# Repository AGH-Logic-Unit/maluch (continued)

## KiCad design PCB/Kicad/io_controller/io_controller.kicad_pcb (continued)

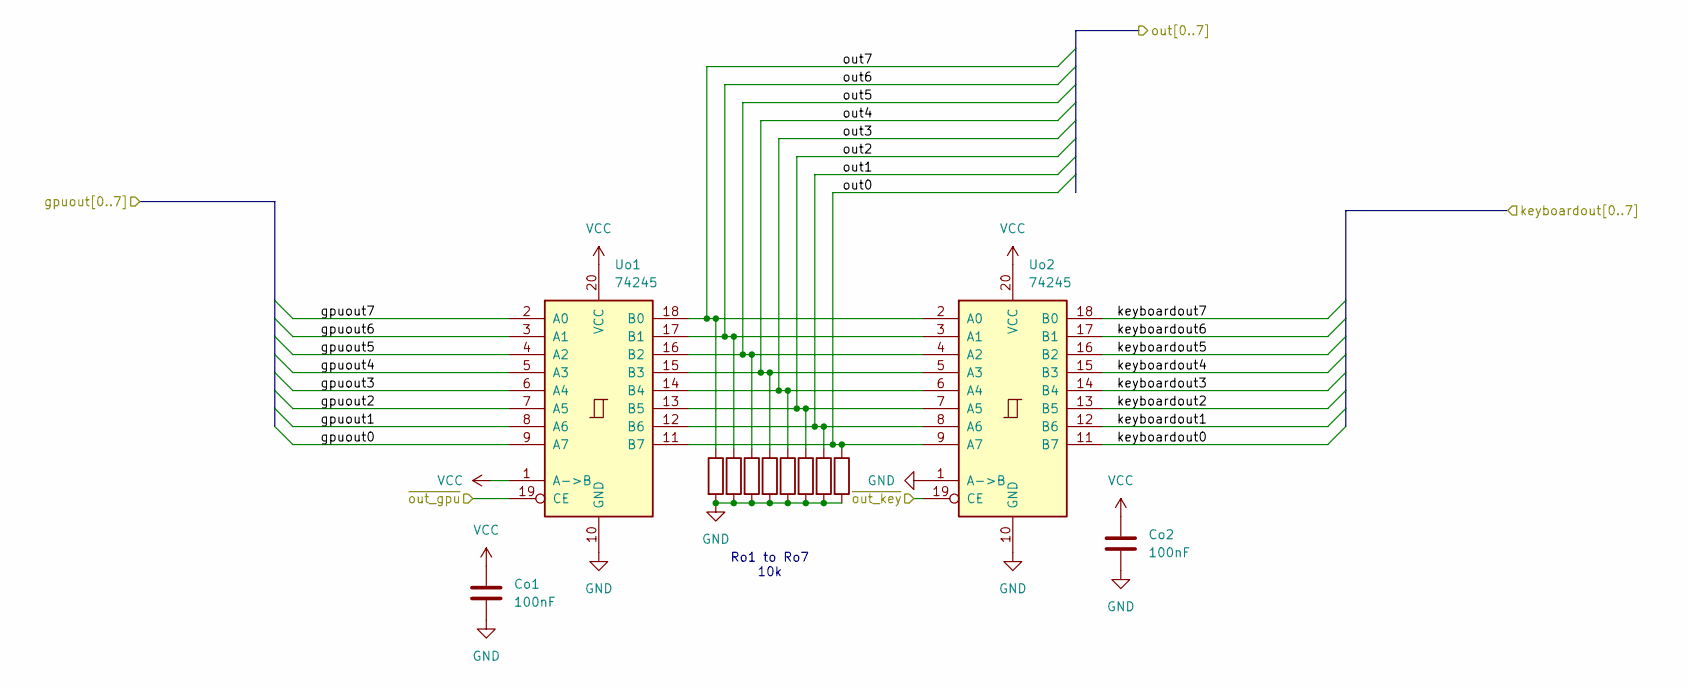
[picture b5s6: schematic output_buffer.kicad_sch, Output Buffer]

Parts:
Co1, Co2: 100nF; C_0402_1005Metric
Ro1, Ro2, Ro3, Ro4, Ro5, Ro6, Ro7, Ro8: 10k; R_0402_1005Metric
Uo1, Uo2: 74245; TSSOP-20_4.4x6.5mm_P0.65mm

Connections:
/decoder/~gpu_out: Uo1.19 (CE); also elsewhere on the board
/decoder/~key_out: Uo2.19 (CE); also elsewhere on the board
/iobus0: Ro8.1, Uo1.11 (B7), Uo2.9 (A7); also elsewhere on the board
/iobus1: Ro7.1, Uo1.12 (B6), Uo2.8 (A6); also elsewhere on the board
/iobus2: Ro6.1, Uo1.13 (B5), Uo2.7 (A5); also elsewhere on the board
/iobus3: Ro5.1, Uo1.14 (B4), Uo2.6 (A4); also elsewhere on the board
/iobus4: Ro4.1, Uo1.15 (B3), Uo2.5 (A3); also elsewhere on the board
/iobus5: Ro3.1, Uo1.16 (B2), Uo2.4 (A2); also elsewhere on the board
/iobus6: Ro2.1, Uo1.17 (B1), Uo2.3 (A1); also elsewhere on the board
/iobus7: Ro1.1, Uo1.18 (B0), Uo2.2 (A0); also elsewhere on the board
/keyout0: Uo2.11 (B7); also elsewhere on the board
/keyout1: Uo2.12 (B6); also elsewhere on the board
/keyout2: Uo2.13 (B5); also elsewhere on the board
/keyout3: Uo2.14 (B4); also elsewhere on the board
/keyout4: Uo2.15 (B3); also elsewhere on the board
/keyout5: Uo2.16 (B2); also elsewhere on the board
/keyout6: Uo2.17 (B1); also elsewhere on the board
/keyout7: Uo2.18 (B0)
GND: Co1.1, Co2.1, Ro1.2, Ro2.2, Ro3.2, Ro4.2, Ro5.2, Ro6.2, Ro7.2, Ro8.2, Uo1.2 (A0), Uo1.3 (A1), Uo1.4 (A2), Uo1.5 (A3), Uo1.6 (A4), Uo1.7 (A5), Uo1.8 (A6), Uo1.10 (GND), Uo2.1 (A->B), Uo2.10 (GND); also elsewhere on the board
VCC: Co1.2, Co2.2, Uo1.1 (A->B), Uo1.9 (A7), Uo1.20 (VCC), Uo2.20 (VCC); also elsewhere on the board

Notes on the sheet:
Ro1 to Ro7 10k

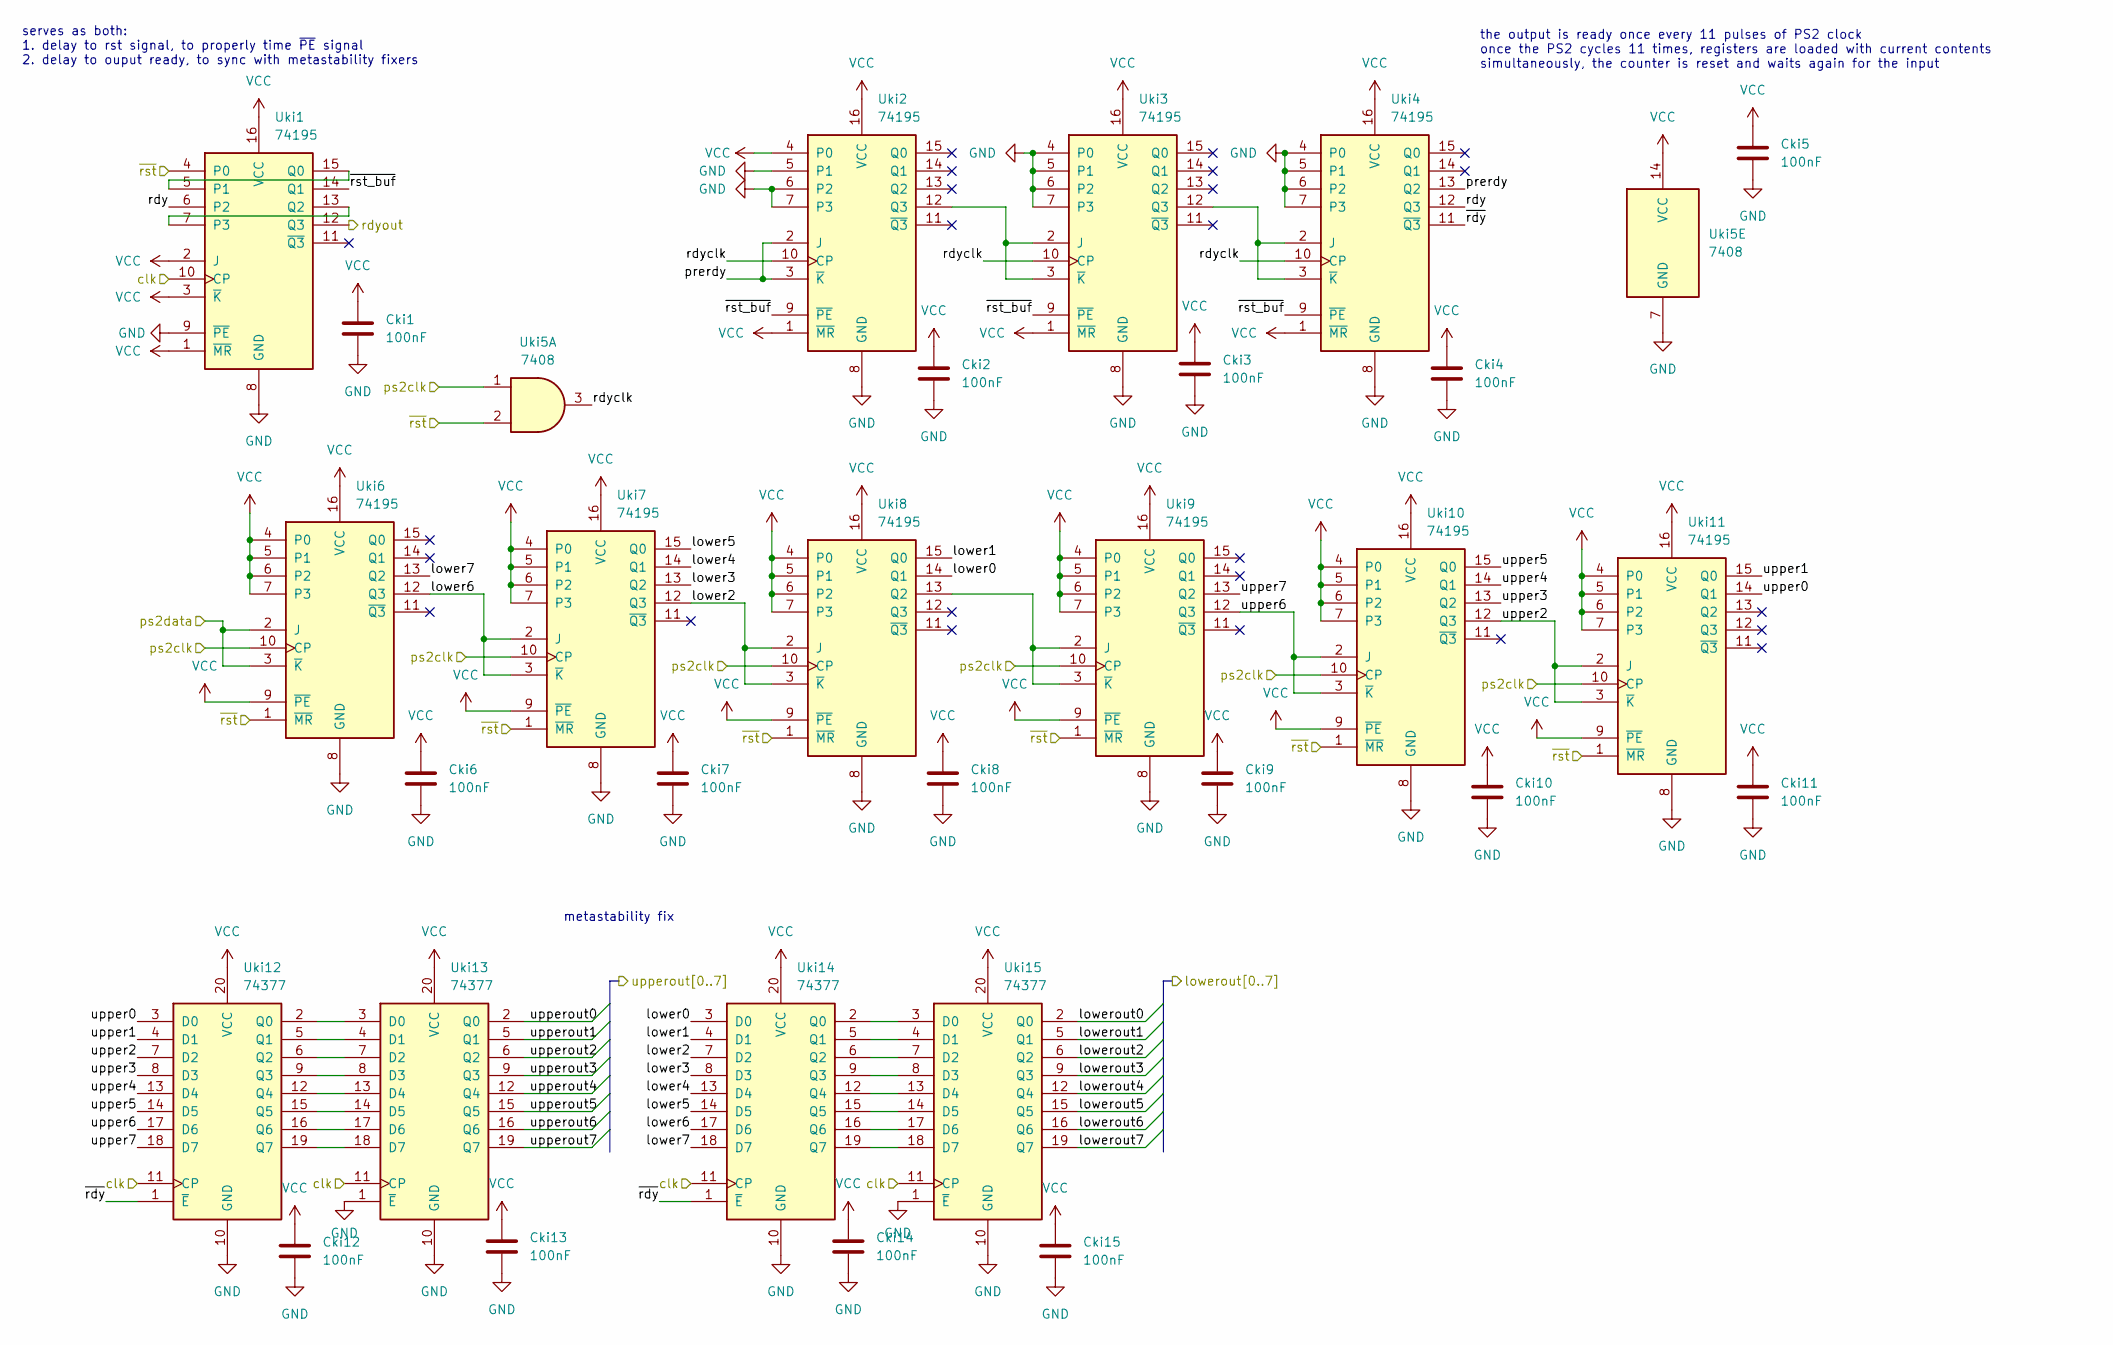
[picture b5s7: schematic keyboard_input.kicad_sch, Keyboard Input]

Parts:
Cki1, Cki2, Cki3, Cki4, Cki5, Cki6, Cki7, Cki8, Cki9, Cki10, Cki11, Cki12, Cki13, Cki14, Cki15: 100nF; C_0402_1005Metric
Uki1, Uki2, Uki3, Uki4, Uki6, Uki7, Uki8, Uki9, Uki10, Uki11: 74195; SOIC-16_3.9x9.9mm_P1.27mm
Uki5: 7408; SO-14_3.9x8.65mm_P1.27mm
Uki12, Uki13, Uki14, Uki15: 74377; SSOP-20_5.3x7.2mm_P0.65mm

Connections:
/clk: Uki1.10 (CP), Uki12.11 (CP), Uki13.11 (CP), Uki14.11 (CP), Uki15.11 (CP); also elsewhere on the board
/keyboard/keyboard_decoder/lower0: Uki15.2 (Q0); also elsewhere on the board
/keyboard/keyboard_decoder/lower1: Uki15.5 (Q1); also elsewhere on the board
/keyboard/keyboard_decoder/lower2: Uki15.6 (Q2); also elsewhere on the board
/keyboard/keyboard_decoder/lower3: Uki15.9 (Q3); also elsewhere on the board
/keyboard/keyboard_decoder/lower4: Uki15.12 (Q4); also elsewhere on the board
/keyboard/keyboard_decoder/lower5: Uki15.15 (Q5); also elsewhere on the board
/keyboard/keyboard_decoder/lower6: Uki15.16 (Q6); also elsewhere on the board
/keyboard/keyboard_decoder/lower7: Uki15.19 (Q7); also elsewhere on the board
/keyboard/keyboard_decoder/rdy: Uki1.12 (Q3); also elsewhere on the board
/keyboard/keyboard_decoder/upper0: Uki13.2 (Q0)
/keyboard/keyboard_decoder/upper1: Uki13.5 (Q1)
/keyboard/keyboard_decoder/upper2: Uki13.6 (Q2)
/keyboard/keyboard_decoder/upper3: Uki13.9 (Q3)
/keyboard/keyboard_decoder/upper4: Uki13.12 (Q4); also elsewhere on the board
/keyboard/keyboard_decoder/upper5: Uki13.15 (Q5); also elsewhere on the board
/keyboard/keyboard_decoder/upper6: Uki13.16 (Q6); also elsewhere on the board
/keyboard/keyboard_decoder/upper7: Uki13.19 (Q7); also elsewhere on the board
/keyboard/keyboard_input/lower0: Uki8.14 (Q1), Uki14.3 (D0)
/keyboard/keyboard_input/lower1: Uki8.15 (Q0), Uki14.4 (D1)
/keyboard/keyboard_input/lower2: Uki7.12 (Q3), Uki8.2 (J), Uki8.3 (~K), Uki14.7 (D2)
/keyboard/keyboard_input/lower3: Uki7.13 (Q2), Uki14.8 (D3)
/keyboard/keyboard_input/lower4: Uki7.14 (Q1), Uki14.13 (D4)
/keyboard/keyboard_input/lower5: Uki7.15 (Q0), Uki14.14 (D5)
/keyboard/keyboard_input/lower6: Uki6.12 (Q3), Uki7.2 (J), Uki7.3 (~K), Uki14.17 (D6)
/keyboard/keyboard_input/lower7: Uki6.13 (Q2), Uki14.18 (D7)
/keyboard/keyboard_input/prerdy: Uki2.2 (J), Uki2.3 (~K), Uki4.13 (Q2)
/keyboard/keyboard_input/rdy: Uki1.6 (P2), Uki4.12 (Q3)
/keyboard/keyboard_input/rdyclk: Uki2.10 (CP), Uki3.10 (CP), Uki4.10 (CP), Uki5.3
/keyboard/keyboard_input/upper0: Uki11.14 (Q1), Uki12.3 (D0)
/keyboard/keyboard_input/upper1: Uki11.15 (Q0), Uki12.4 (D1)
/keyboard/keyboard_input/upper2: Uki10.12 (Q3), Uki11.2 (J), Uki11.3 (~K), Uki12.7 (D2)
/keyboard/keyboard_input/upper3: Uki10.13 (Q2), Uki12.8 (D3)
/keyboard/keyboard_input/upper4: Uki10.14 (Q1), Uki12.13 (D4)
/keyboard/keyboard_input/upper5: Uki10.15 (Q0), Uki12.14 (D5)
/keyboard/keyboard_input/upper6: Uki9.12 (Q3), Uki10.2 (J), Uki10.3 (~K), Uki12.17 (D6)
/keyboard/keyboard_input/upper7: Uki9.13 (Q2), Uki12.18 (D7)
/keyboard/keyboard_input/~rdy: Uki4.11 (~Q3), Uki12.1 (~E), Uki14.1 (~E)
/keyboard/keyboard_input/~rst_buf: Uki1.14 (Q1), Uki2.9 (~PE), Uki3.9 (~PE), Uki4.9 (~PE)
/keyboard_enable: Uki1.4 (P0), Uki5.2, Uki6.1 (~MR), Uki7.1 (~MR), Uki8.1 (~MR), Uki9.1 (~MR), Uki10.1 (~MR), Uki11.1 (~MR); also elsewhere on the board
/ps2clk: Uki5.1, Uki6.10 (CP), Uki7.10 (CP), Uki8.10 (CP), Uki9.10 (CP), Uki10.10 (CP), Uki11.10 (CP); also elsewhere on the board
/ps2data: Uki6.2 (J), Uki6.3 (~K); also elsewhere on the board
GND: Cki1.2, Cki2.2, Cki3.2, Cki4.2, Cki5.2, Cki6.2, Cki7.2, Cki8.2, Cki9.2, Cki10.2, Cki11.2, Cki12.2, Cki13.2, Cki14.2, Cki15.2, Uki1.8 (GND), Uki1.9 (~PE), Uki2.5 (P1), Uki2.6 (P2), Uki2.7 (P3), Uki2.8 (GND), Uki3.4 (P0), Uki3.5 (P1), Uki3.6 (P2), Uki3.7 (P3), Uki3.8 (GND), Uki4.4 (P0), Uki4.5 (P1), Uki4.6 (P2), Uki4.7 (P3), Uki4.8 (GND), Uki5.7 (GND), Uki6.8 (GND), Uki7.8 (GND), Uki8.8 (GND), Uki9.8 (GND), Uki10.8 (GND), Uki11.8 (GND), Uki12.10 (GND), Uki13.1 (~E), Uki13.10 (GND), Uki14.10 (GND), Uki15.1 (~E), Uki15.10 (GND); also elsewhere on the board
unnamed: Uki1.5 (P1), Uki1.15 (Q0)
unnamed: Uki1.7 (P3), Uki1.13 (Q2)
unnamed: Uki2.12 (Q3), Uki3.2 (J), Uki3.3 (~K)
unnamed: Uki3.12 (Q3), Uki4.2 (J), Uki4.3 (~K)
unnamed: Uki8.13 (Q2), Uki9.2 (J), Uki9.3 (~K)
unnamed: Uki12.2 (Q0), Uki13.3 (D0)
unnamed: Uki12.5 (Q1), Uki13.4 (D1)
unnamed: Uki12.6 (Q2), Uki13.7 (D2)
unnamed: Uki12.9 (Q3), Uki13.8 (D3)
unnamed: Uki12.12 (Q4), Uki13.13 (D4)
unnamed: Uki12.15 (Q5), Uki13.14 (D5)
unnamed: Uki12.16 (Q6), Uki13.17 (D6)
unnamed: Uki12.19 (Q7), Uki13.18 (D7)
unnamed: Uki14.2 (Q0), Uki15.3 (D0)
unnamed: Uki14.5 (Q1), Uki15.4 (D1)
unnamed: Uki14.6 (Q2), Uki15.7 (D2)
unnamed: Uki14.9 (Q3), Uki15.8 (D3)
unnamed: Uki14.12 (Q4), Uki15.13 (D4)
unnamed: Uki14.15 (Q5), Uki15.14 (D5)
unnamed: Uki14.16 (Q6), Uki15.17 (D6)
unnamed: Uki14.19 (Q7), Uki15.18 (D7)
VCC: Cki1.1, Cki2.1, Cki3.1, Cki4.1, Cki5.1, Cki6.1, Cki7.1, Cki8.1, Cki9.1, Cki10.1, Cki11.1, Cki12.1, Cki13.1, Cki14.1, Cki15.1, Uki1.1 (~MR), Uki1.2 (J), Uki1.3 (~K), Uki1.16 (VCC), Uki2.1 (~MR), Uki2.4 (P0), Uki2.16 (VCC), Uki3.1 (~MR), Uki3.16 (VCC), Uki4.1 (~MR), Uki4.16 (VCC), Uki5.14 (VCC), Uki6.4 (P0), Uki6.5 (P1), Uki6.6 (P2), Uki6.7 (P3), Uki6.9 (~PE), Uki6.16 (VCC), Uki7.4 (P0), Uki7.5 (P1), Uki7.6 (P2), Uki7.7 (P3), Uki7.9 (~PE), Uki7.16 (VCC), Uki8.4 (P0), Uki8.5 (P1), Uki8.6 (P2), Uki8.7 (P3), Uki8.9 (~PE), Uki8.16 (VCC), Uki9.4 (P0), Uki9.5 (P1), Uki9.6 (P2), Uki9.7 (P3), Uki9.9 (~PE), Uki9.16 (VCC), Uki10.4 (P0), Uki10.5 (P1), Uki10.6 (P2), Uki10.7 (P3), Uki10.9 (~PE), Uki10.16 (VCC), Uki11.4 (P0), Uki11.5 (P1), Uki11.6 (P2), Uki11.7 (P3), Uki11.9 (~PE), Uki11.16 (VCC), Uki12.20 (VCC), Uki13.20 (VCC), Uki14.20 (VCC), Uki15.20 (VCC); also elsewhere on the board

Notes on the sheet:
metastability fix
serves as both: 1. delay to rst signal, to properly time ~{PE} signal 2. delay to ouput ready, to sync with metastability fixers
the output is ready once every 11 pulses of PS2 clock once the PS2 cycles 11 times, registers are loaded with current contents simultaneously, the counter is reset and waits again for the input

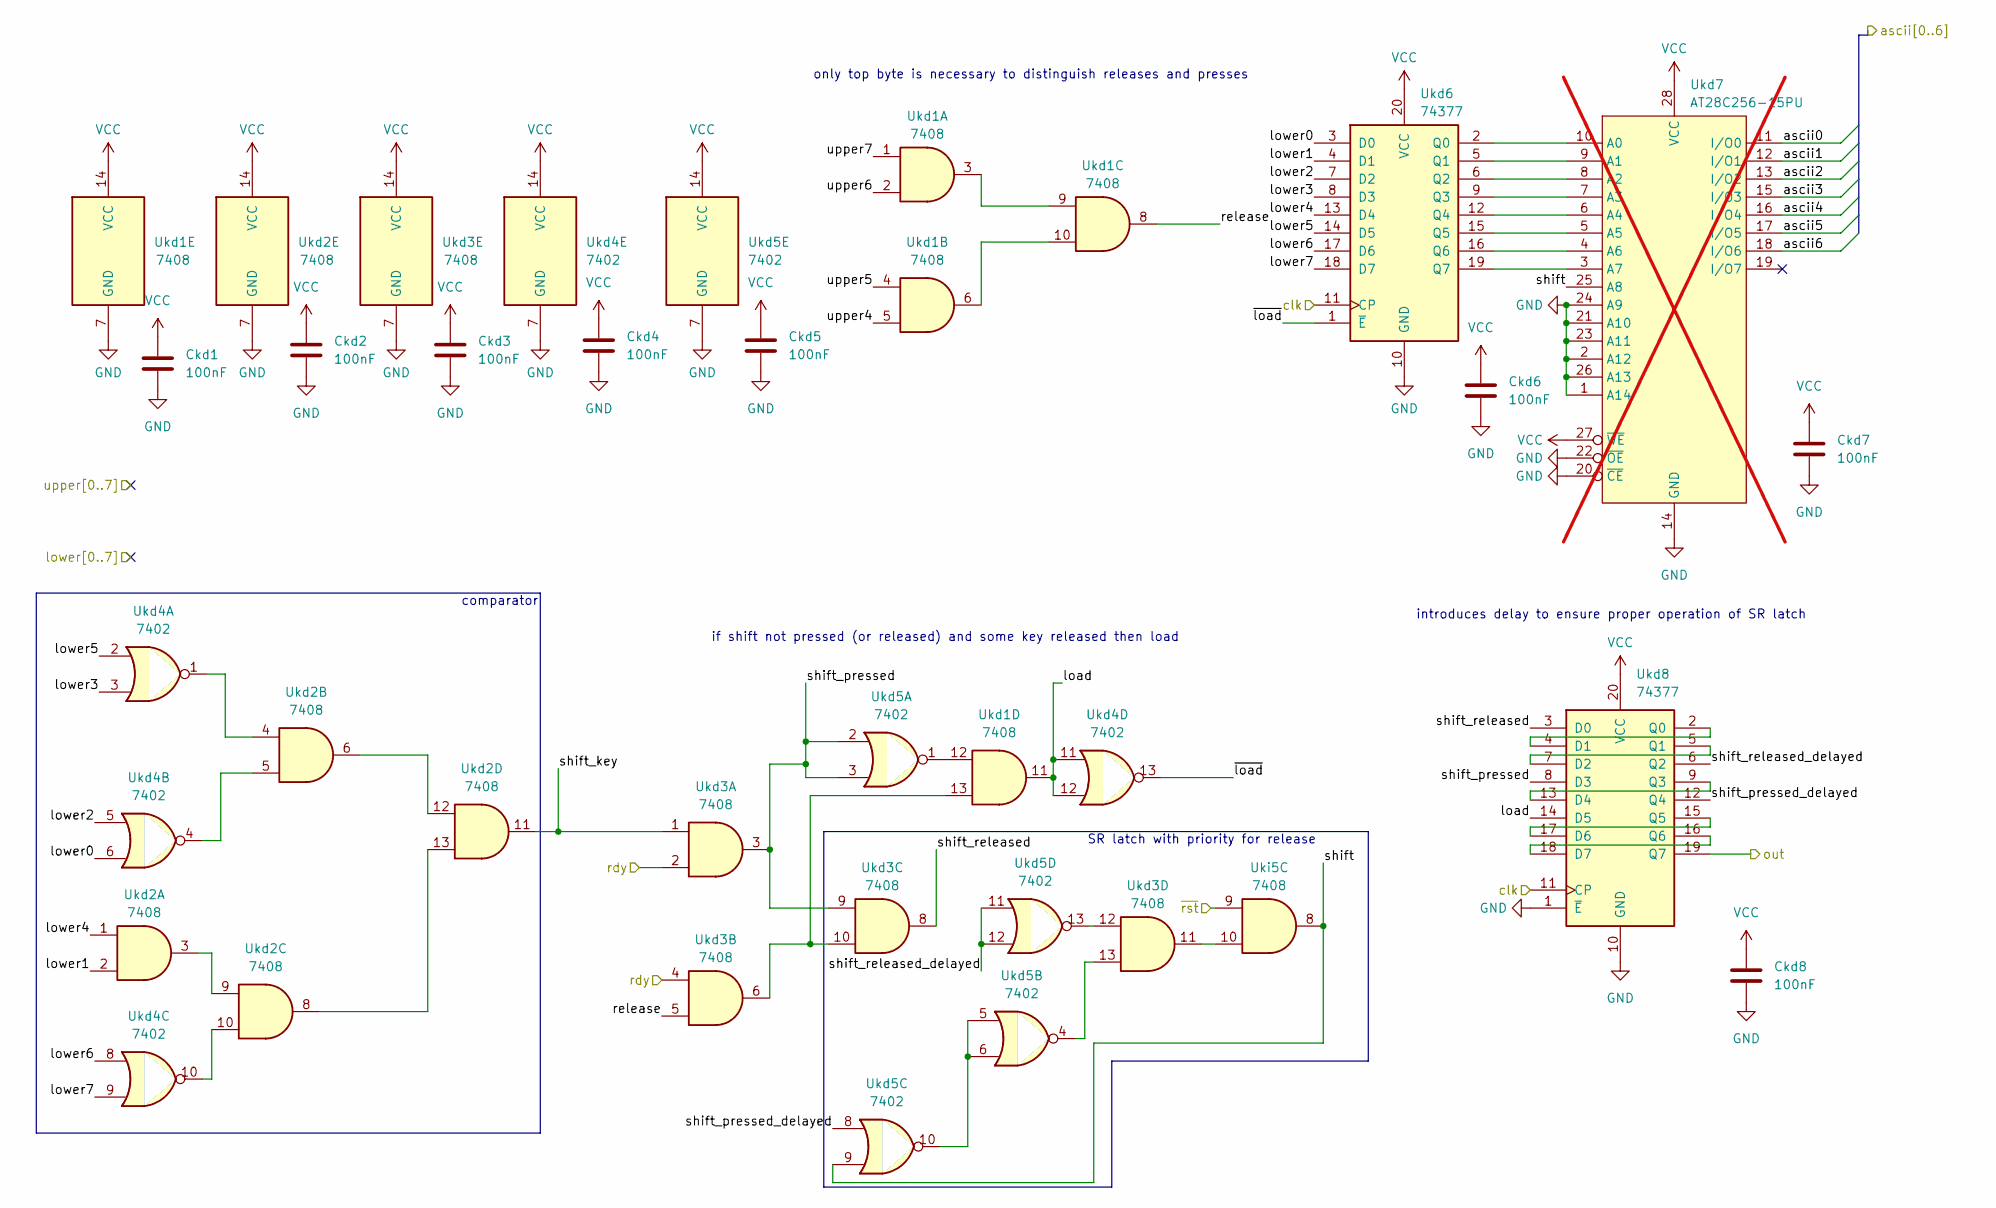
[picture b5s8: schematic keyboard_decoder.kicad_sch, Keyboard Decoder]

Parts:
Ckd1, Ckd2, Ckd3, Ckd4, Ckd5, Ckd6, Ckd7, Ckd8: 100nF; C_0402_1005Metric
Ukd1, Ukd2, Ukd3: 7408; SO-14_3.9x8.65mm_P1.27mm
Ukd4, Ukd5: 7402; SOIC-14_3.9x8.7mm_P1.27mm
Ukd6, Ukd8: 74377; SSOP-20_5.3x7.2mm_P0.65mm
Ukd7: AT28C256-15PU; DIP-28_W15.24mm_Socket; not fitted
Uki5: 7408; SO-14_3.9x8.65mm_P1.27mm

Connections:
/clk: Ukd6.11 (CP), Ukd8.11 (CP); also elsewhere on the board
/keyboard/keyboard_decoder/load: Ukd1.11, Ukd4.11, Ukd4.12, Ukd8.14 (D5)
/keyboard/keyboard_decoder/lower0: Ukd4.6, Ukd6.3 (D0); also elsewhere on the board
/keyboard/keyboard_decoder/lower1: Ukd2.2, Ukd6.4 (D1); also elsewhere on the board
/keyboard/keyboard_decoder/lower2: Ukd4.5, Ukd6.7 (D2); also elsewhere on the board
/keyboard/keyboard_decoder/lower3: Ukd4.3, Ukd6.8 (D3); also elsewhere on the board
/keyboard/keyboard_decoder/lower4: Ukd2.1, Ukd6.13 (D4); also elsewhere on the board
/keyboard/keyboard_decoder/lower5: Ukd4.2, Ukd6.14 (D5); also elsewhere on the board
/keyboard/keyboard_decoder/lower6: Ukd4.8, Ukd6.17 (D6); also elsewhere on the board
/keyboard/keyboard_decoder/lower7: Ukd4.9, Ukd6.18 (D7); also elsewhere on the board
/keyboard/keyboard_decoder/rdy: Ukd3.2, Ukd3.4; also elsewhere on the board
/keyboard/keyboard_decoder/release: Ukd1.8, Ukd3.5
/keyboard/keyboard_decoder/shift: Ukd5.9, Ukd7.25 (A8), Uki5.8
/keyboard/keyboard_decoder/shift_key: Ukd2.11, Ukd3.1
/keyboard/keyboard_decoder/shift_pressed: Ukd3.3, Ukd3.9, Ukd5.2, Ukd5.3, Ukd8.8 (D3)
/keyboard/keyboard_decoder/shift_pressed_delayed: Ukd5.8, Ukd8.12 (Q4)
/keyboard/keyboard_decoder/shift_released: Ukd3.8, Ukd8.3 (D0)
/keyboard/keyboard_decoder/shift_released_delayed: Ukd5.11, Ukd5.12, Ukd8.6 (Q2)
/keyboard/keyboard_decoder/upper4: Ukd1.5; also elsewhere on the board
/keyboard/keyboard_decoder/upper5: Ukd1.4; also elsewhere on the board
/keyboard/keyboard_decoder/upper6: Ukd1.2; also elsewhere on the board
/keyboard/keyboard_decoder/upper7: Ukd1.1; also elsewhere on the board
/keyboard/keyboard_decoder/~load: Ukd4.13, Ukd6.1 (~E)
/keyboard/newkey: Ukd8.19 (Q7); also elsewhere on the board
/keyboard_enable: Uki5.9; also elsewhere on the board
/keyout0: Ukd7.11 (I/O0); also elsewhere on the board
/keyout1: Ukd7.12 (I/O1); also elsewhere on the board
/keyout2: Ukd7.13 (I/O2); also elsewhere on the board
/keyout3: Ukd7.15 (I/O3); also elsewhere on the board
/keyout4: Ukd7.16 (I/O4); also elsewhere on the board
/keyout5: Ukd7.17 (I/O5); also elsewhere on the board
/keyout6: Ukd7.18 (I/O6); also elsewhere on the board
GND: Ckd1.2, Ckd2.2, Ckd3.2, Ckd4.2, Ckd5.2, Ckd6.2, Ckd7.2, Ckd8.2, Ukd1.7 (GND), Ukd2.7 (GND), Ukd3.7 (GND), Ukd4.7 (GND), Ukd5.7 (GND), Ukd6.10 (GND), Ukd7.1 (A14), Ukd7.2 (A12), Ukd7.14 (GND), Ukd7.20 (~CE), Ukd7.21 (A10), Ukd7.22 (~OE), Ukd7.23 (A11), Ukd7.24 (A9), Ukd7.26 (A13), Ukd8.1 (~E), Ukd8.10 (GND); also elsewhere on the board
unnamed: Ukd1.3, Ukd1.9
unnamed: Ukd1.6, Ukd1.10
unnamed: Ukd1.12, Ukd5.1
unnamed: Ukd1.13, Ukd3.6, Ukd3.10
unnamed: Ukd2.3, Ukd2.9
unnamed: Ukd2.4, Ukd4.1
unnamed: Ukd2.5, Ukd4.4
unnamed: Ukd2.10, Ukd4.10
unnamed: Ukd2.6, Ukd2.12
unnamed: Ukd2.8, Ukd2.13
unnamed: Ukd3.11, Uki5.10
unnamed: Ukd3.12, Ukd5.13
unnamed: Ukd3.13, Ukd5.4
unnamed: Ukd5.5, Ukd5.6, Ukd5.10
unnamed: Ukd6.2 (Q0), Ukd7.10 (A0)
unnamed: Ukd6.5 (Q1), Ukd7.9 (A1)
unnamed: Ukd6.6 (Q2), Ukd7.8 (A2)
unnamed: Ukd6.9 (Q3), Ukd7.7 (A3)
unnamed: Ukd6.12 (Q4), Ukd7.6 (A4)
unnamed: Ukd6.15 (Q5), Ukd7.5 (A5)
unnamed: Ukd6.16 (Q6), Ukd7.4 (A6)
unnamed: Ukd6.19 (Q7), Ukd7.3 (A7)
unnamed: Ukd8.2 (Q0), Ukd8.4 (D1)
unnamed: Ukd8.5 (Q1), Ukd8.7 (D2)
unnamed: Ukd8.9 (Q3), Ukd8.13 (D4)
unnamed: Ukd8.15 (Q5), Ukd8.17 (D6)
unnamed: Ukd8.16 (Q6), Ukd8.18 (D7)
VCC: Ckd1.1, Ckd2.1, Ckd3.1, Ckd4.1, Ckd5.1, Ckd6.1, Ckd7.1, Ckd8.1, Ukd1.14 (VCC), Ukd2.14 (VCC), Ukd3.14 (VCC), Ukd4.14 (VCC), Ukd5.14 (VCC), Ukd6.20 (VCC), Ukd7.27 (~WE), Ukd7.28 (VCC), Ukd8.20 (VCC); also elsewhere on the board

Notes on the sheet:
introduces delay to ensure proper operation of SR latch
only top byte is necessary to distinguish releases and presses
if shift not pressed (or released) and some key released then load
comparator
SR latch with priority for release

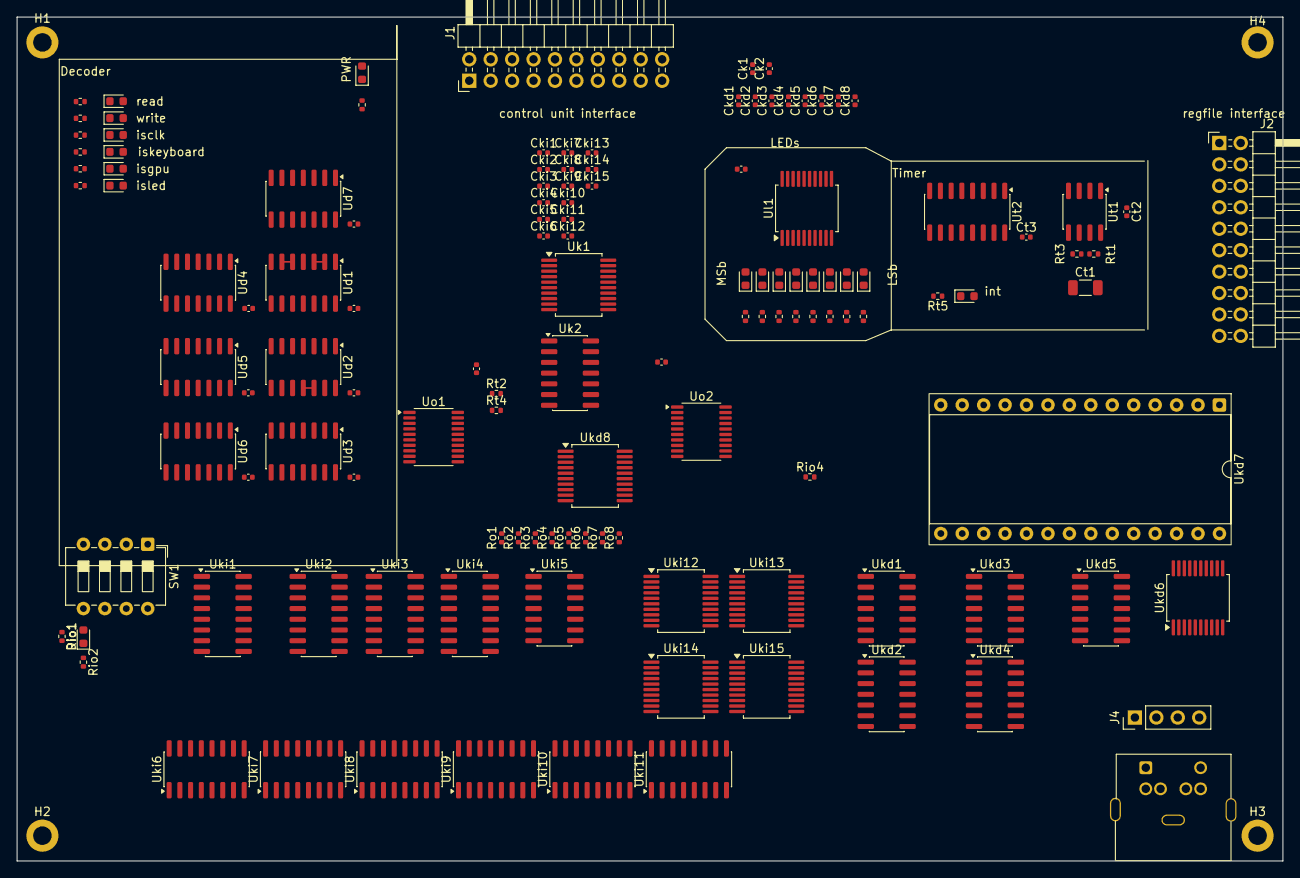
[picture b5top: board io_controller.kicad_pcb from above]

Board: 6 copper layers, 150.0 x 100.0 mm, 132 parts (0 on the bottom side), 185 nets.

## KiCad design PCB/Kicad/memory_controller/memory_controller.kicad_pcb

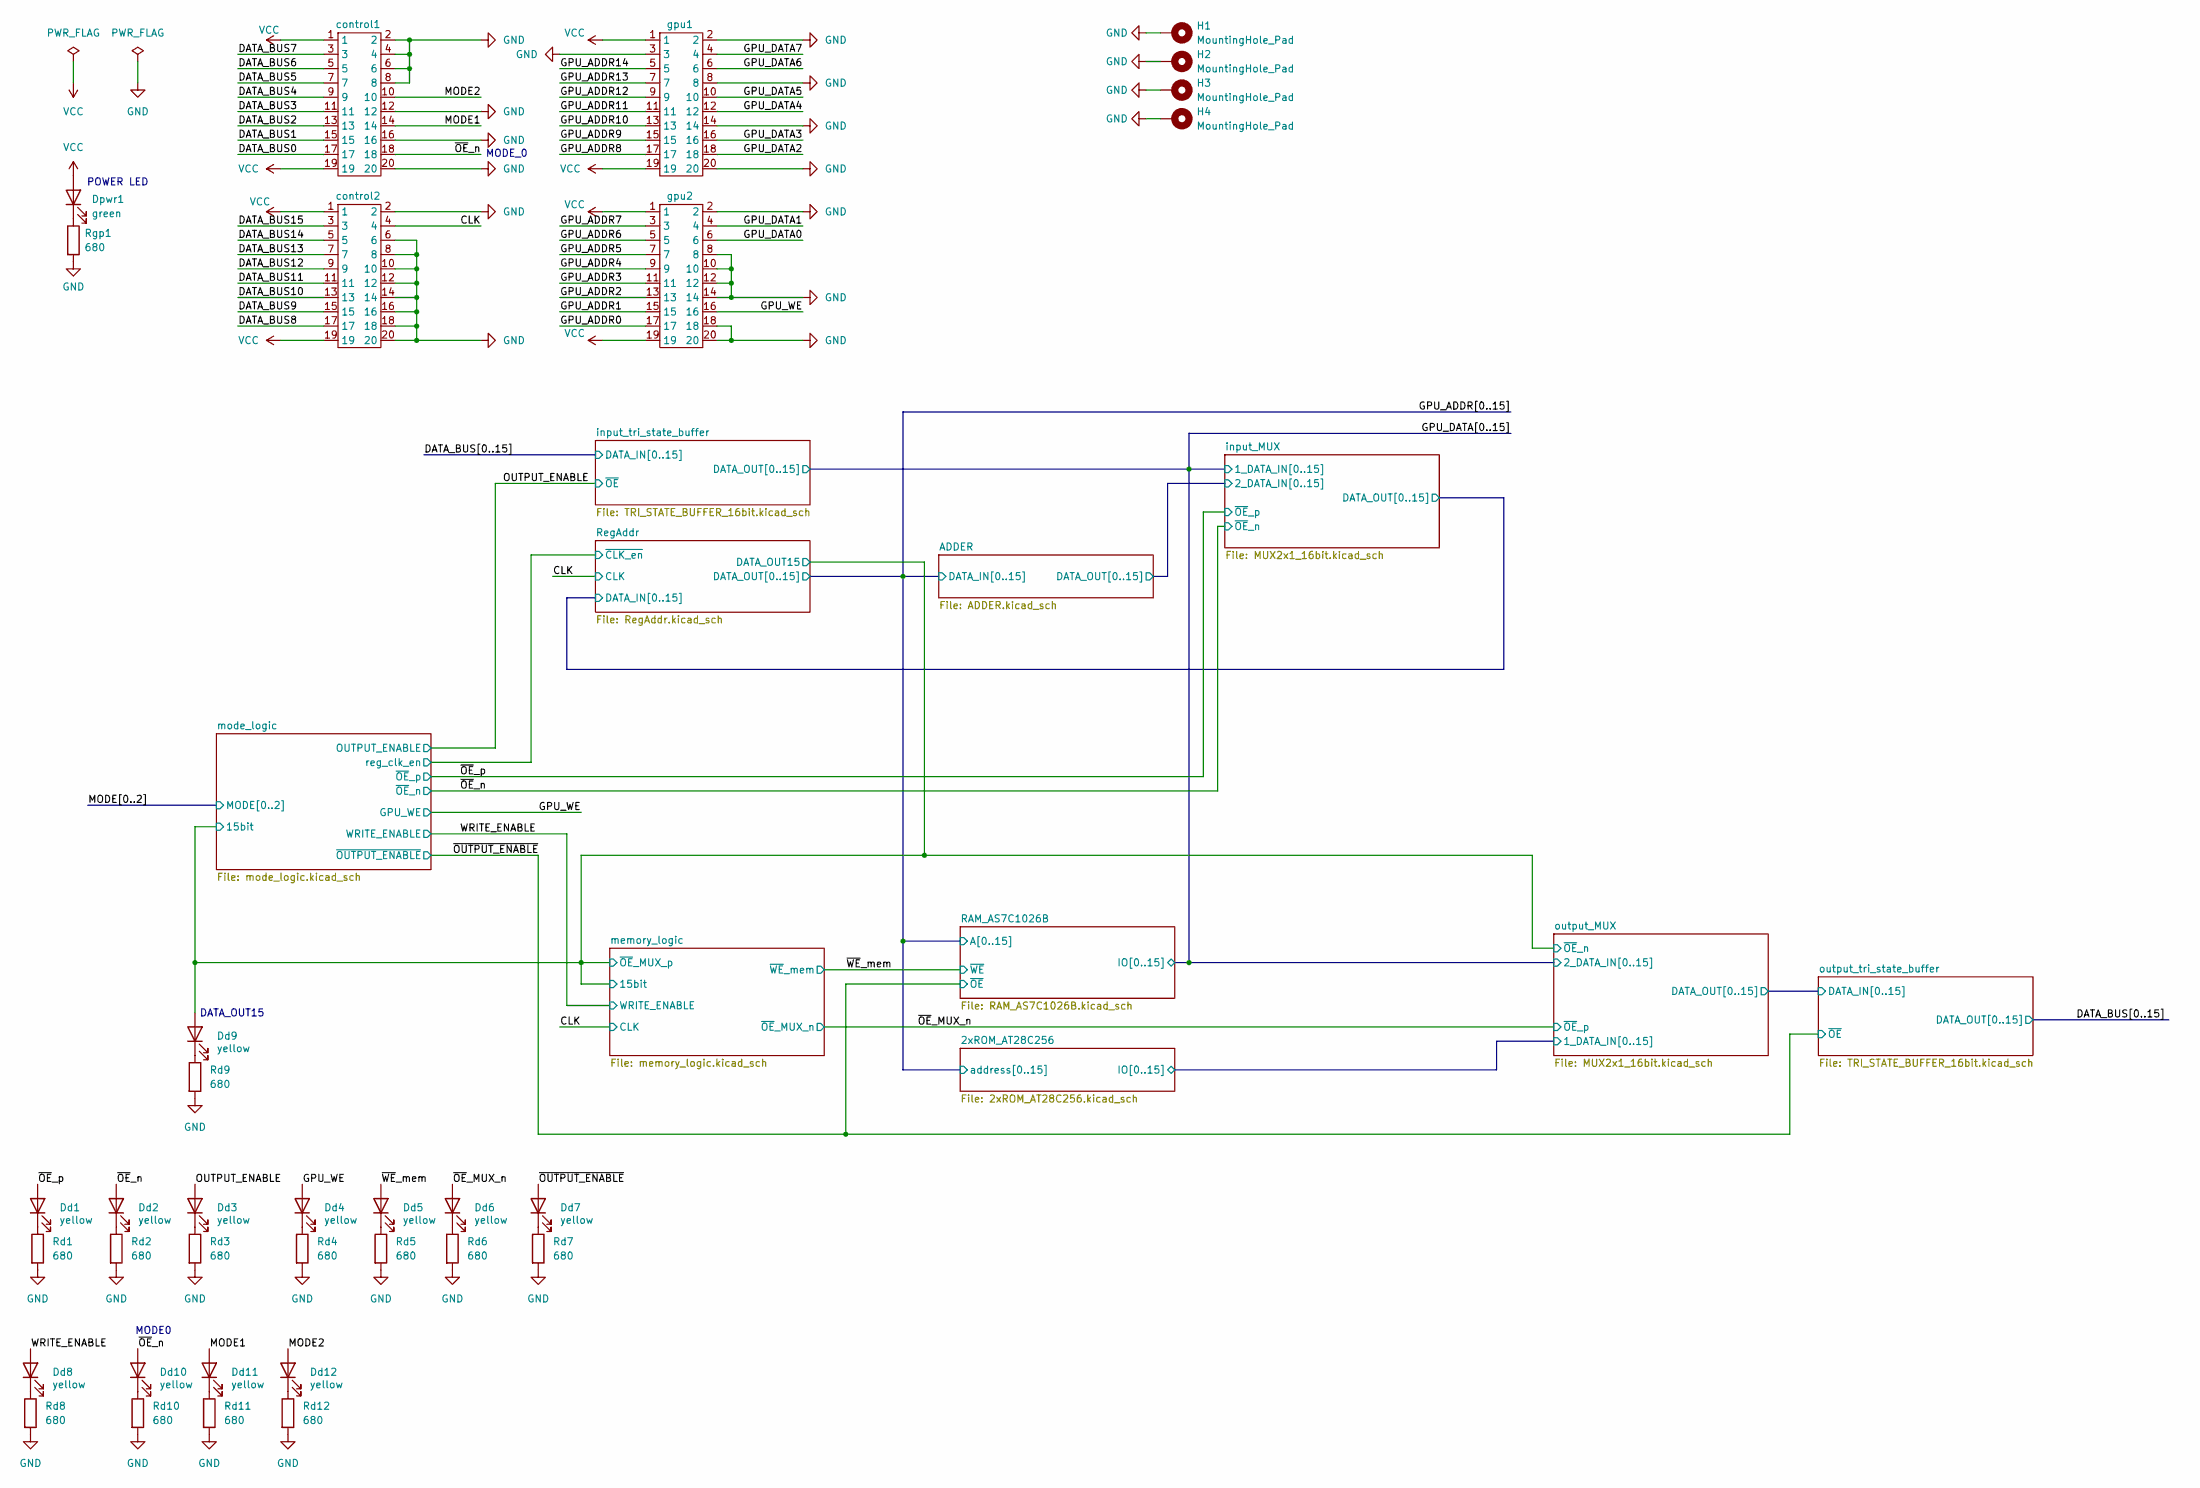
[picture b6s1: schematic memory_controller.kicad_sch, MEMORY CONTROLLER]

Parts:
Dd1, Dd2, Dd3, Dd4, Dd5, Dd6, Dd7, Dd8, Dd9, Dd10, Dd11, Dd12: yellow; LED_0603_1608Metric
Dpwr1: green; LED_0603_1608Metric
H1, H2, H3, H4: MountingHole_Pad; MountingHole_2.2mm_M2_DIN965_Pad
Rd1, Rd2, Rd3, Rd4, Rd5, Rd6, Rd7, Rd8, Rd9, Rd10, Rd11, Rd12: 680; R_0402_1005Metric
Rgp1: 680; R_0402_1005Metric
control1, control2: out; PinHeader_2x10_P2.54mm_Horizontal
gpu1, gpu2: in; PinHeader_2x10_P2.54mm_Horizontal

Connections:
/CLK: control2.4; also elsewhere on the board
/DATA_BUS0: control1.17; also elsewhere on the board
/DATA_BUS1: control1.15; also elsewhere on the board
/DATA_BUS2: control1.13; also elsewhere on the board
/DATA_BUS3: control1.11; also elsewhere on the board
/DATA_BUS4: control1.9; also elsewhere on the board
/DATA_BUS5: control1.7; also elsewhere on the board
/DATA_BUS6: control1.5; also elsewhere on the board
/DATA_BUS7: control1.3; also elsewhere on the board
/DATA_BUS8: control2.17; also elsewhere on the board
/DATA_BUS9: control2.15; also elsewhere on the board
/DATA_BUS10: control2.13; also elsewhere on the board
/DATA_BUS11: control2.11; also elsewhere on the board
/DATA_BUS12: control2.9; also elsewhere on the board
/DATA_BUS13: control2.7; also elsewhere on the board
/DATA_BUS14: control2.5; also elsewhere on the board
/DATA_BUS15: control2.3; also elsewhere on the board
/GPU_ADDR0: gpu2.17; also elsewhere on the board
/GPU_ADDR1: gpu2.15; also elsewhere on the board
/GPU_ADDR2: gpu2.13; also elsewhere on the board
/GPU_ADDR3: gpu2.11; also elsewhere on the board
/GPU_ADDR4: gpu2.9; also elsewhere on the board
/GPU_ADDR5: gpu2.7; also elsewhere on the board
/GPU_ADDR6: gpu2.5; also elsewhere on the board
/GPU_ADDR7: gpu2.3; also elsewhere on the board
/GPU_ADDR8: gpu1.17; also elsewhere on the board
/GPU_ADDR9: gpu1.15; also elsewhere on the board
/GPU_ADDR10: gpu1.13; also elsewhere on the board
/GPU_ADDR11: gpu1.11; also elsewhere on the board
/GPU_ADDR12: gpu1.9; also elsewhere on the board
/GPU_ADDR13: gpu1.7; also elsewhere on the board
/GPU_ADDR14: gpu1.5; also elsewhere on the board
/GPU_ADDR15: Dd9.2 (A); also elsewhere on the board
/GPU_DATA0: gpu2.6; also elsewhere on the board
/GPU_DATA1: gpu2.4; also elsewhere on the board
/GPU_DATA2: gpu1.18; also elsewhere on the board
/GPU_DATA3: gpu1.16; also elsewhere on the board
/GPU_DATA4: gpu1.12; also elsewhere on the board
/GPU_DATA5: gpu1.10; also elsewhere on the board
/GPU_DATA6: gpu1.6; also elsewhere on the board
/GPU_DATA7: gpu1.4; also elsewhere on the board
/GPU_WE: Dd4.2 (A), gpu2.16; also elsewhere on the board
/MODE1: Dd11.2 (A), control1.14; also elsewhere on the board
/MODE2: Dd12.2 (A), control1.10; also elsewhere on the board
/OUTPUT_ENABLE: Dd3.2 (A); also elsewhere on the board
/WRITE_ENABLE: Dd8.2 (A); also elsewhere on the board
/~OE_MUX_n: Dd6.2 (A); also elsewhere on the board
/~OE_n: Dd2.2 (A), Dd10.2 (A), control1.18; also elsewhere on the board
/~OE_p: Dd1.2 (A); also elsewhere on the board
/~OUTPUT_ENABLE: Dd7.2 (A); also elsewhere on the board
/~WE_mem: Dd5.2 (A); also elsewhere on the board
GND: H1.1 (1_1), H2.1 (1_1), H3.1 (1_1), H4.1 (1_1), Rd1.2, Rd2.2, Rd3.2, Rd4.2, Rd5.2, Rd6.2, Rd7.2, Rd8.2, Rd9.2, Rd10.2, Rd11.2, Rd12.2, Rgp1.2, control1.2, control1.4, control1.6, control1.8, control1.12, control1.16, control1.20, control2.2, control2.6, control2.8, control2.10, control2.12, control2.14, control2.16, control2.18, control2.20, gpu1.2, gpu1.3, gpu1.8, gpu1.14, gpu1.20, gpu2.2, gpu2.8, gpu2.10, gpu2.12, gpu2.14, gpu2.18, gpu2.20; also elsewhere on the board
unnamed: Dd1.1 (K), Rd1.1
unnamed: Dd2.1 (K), Rd2.1
unnamed: Dd3.1 (K), Rd3.1
unnamed: Dd4.1 (K), Rd4.1
unnamed: Dd5.1 (K), Rd5.1
unnamed: Dd6.1 (K), Rd6.1
unnamed: Dd7.1 (K), Rd7.1
unnamed: Dd8.1 (K), Rd8.1
unnamed: Dd9.1 (K), Rd9.1
unnamed: Dd10.1 (K), Rd10.1
unnamed: Dd11.1 (K), Rd11.1
unnamed: Dd12.1 (K), Rd12.1
unnamed: Dpwr1.1 (K), Rgp1.1
VCC: Dpwr1.2 (A), control1.1, control1.19, control2.1, control2.19, gpu1.1, gpu1.19, gpu2.1, gpu2.19; also elsewhere on the board

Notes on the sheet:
MODE0
DATA_OUT15
POWER LED
MODE_0
